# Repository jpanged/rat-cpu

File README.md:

# RAT CPU
*For CPE 233 Winter 2018*

**Russell Caletena, Josiah Pang, & Nathan Wang**

This repository contains all the parts that make up the RAT CPU as well as the software programs written in Assembly.

## [Learn more at our project website!](https://jpanged.github.io/rat-cpu/)

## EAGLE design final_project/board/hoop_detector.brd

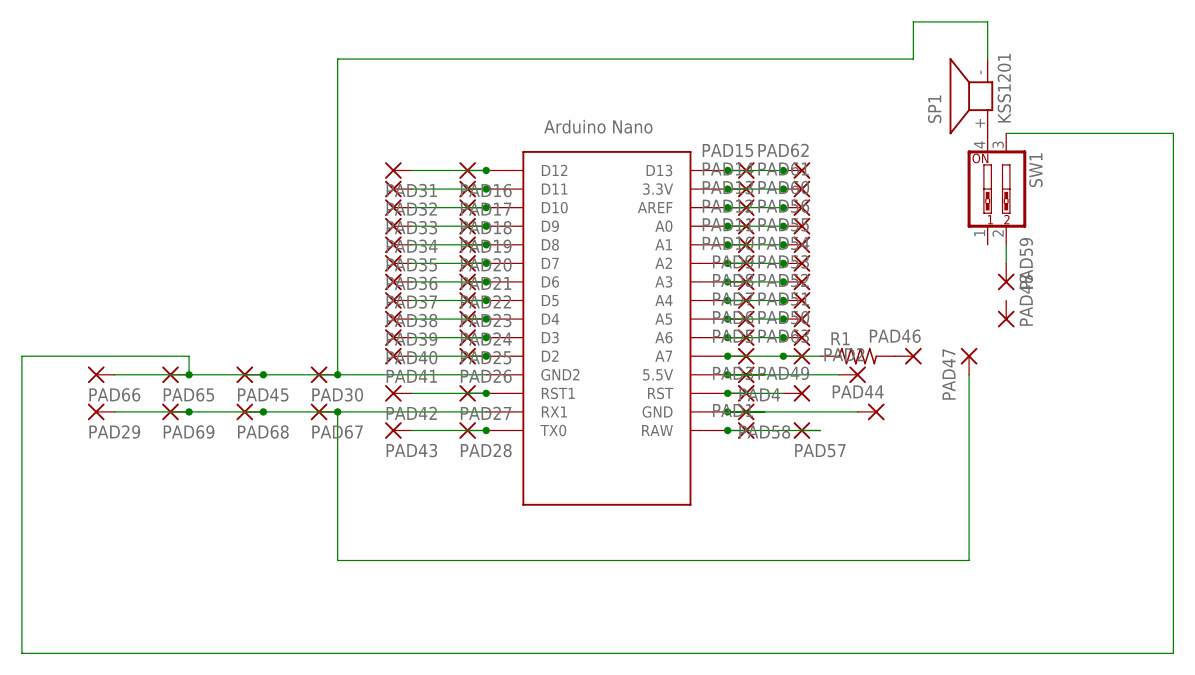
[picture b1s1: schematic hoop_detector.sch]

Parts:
PAD1, PAD2, PAD3, PAD4, PAD5, PAD6, PAD7, PAD8, PAD9, PAD10, PAD11, PAD12, PAD13, PAD14, PAD15, PAD16, PAD17, PAD18, PAD19, PAD20, PAD21, PAD22, PAD23, PAD24, PAD25, PAD26, PAD27, PAD28, PAD29, PAD30, PAD31, PAD32, PAD33, PAD34, PAD35, PAD36, PAD37, PAD38, PAD39, PAD40, PAD41, PAD42, PAD43, PAD44, PAD45, PAD46, PAD47, PAD48, PAD49, PAD50, PAD51, PAD52, PAD53, PAD54, PAD55, PAD56, PAD57, PAD58, PAD59, PAD60, PAD61, PAD62, PAD63, PAD65, PAD66, PAD67, PAD68, PAD69: 1,6/0,9
R1: R-US_0204/7; 0204/7
SP1: KSS1201
SW1: SW_DIP-2; EDG-02
U$1: NANO

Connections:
unnamed: PAD18.1, PAD33.1, U$1.D10
unnamed: PAD19.1, PAD34.1, U$1.D9
unnamed: PAD20.1, PAD35.1, U$1.D8
unnamed: PAD21.1, PAD36.1, U$1.D7
unnamed: PAD22.1, PAD37.1, U$1.D6
unnamed: PAD23.1, PAD38.1, U$1.D5
unnamed: PAD24.1, PAD39.1, U$1.D4
unnamed: PAD25.1, PAD40.1, U$1.D3
unnamed: PAD26.1, PAD41.1, U$1.D2
unnamed: PAD27.1, PAD42.1, U$1.RST1
unnamed: PAD28.1, PAD43.1, U$1.TX0
unnamed: PAD29.1, PAD47.1, PAD67.1, PAD68.1, PAD69.1, U$1.RX1
unnamed: PAD30.1, PAD45.1, PAD65.1, PAD66.1, SW1.3, U$1.GND1 (GND2)
unnamed: PAD16.1, PAD31.1, U$1.D12
unnamed: PAD17.1, PAD32.1, U$1.D11
unnamed: PAD59.1, SW1.2
unnamed: SP1.+ (1), SW1.4
unnamed: PAD5.1, PAD63.1, R1.1, U$1.A7
unnamed: PAD2.1, PAD4.1, U$1.5V (5.5V)
unnamed: PAD3.1, PAD49.1, U$1.RST
unnamed: PAD44.1, PAD58.1, U$1.GND
unnamed: PAD1.1, PAD57.1, U$1.RAW
unnamed: PAD46.1, R1.2
unnamed: PAD14.1, PAD61.1, U$1.3.3V
unnamed: PAD13.1, PAD60.1, U$1.AREF
unnamed: PAD12.1, PAD56.1, U$1.A0
unnamed: PAD10.1, PAD54.1, U$1.A2
unnamed: PAD9.1, PAD53.1, U$1.A3
unnamed: PAD8.1, PAD52.1, U$1.A4
unnamed: PAD7.1, PAD51.1, U$1.A5
unnamed: PAD6.1, PAD50.1, U$1.A6
unnamed: PAD11.1, PAD55.1, U$1.A1
unnamed: PAD15.1, PAD62.1, U$1.D13

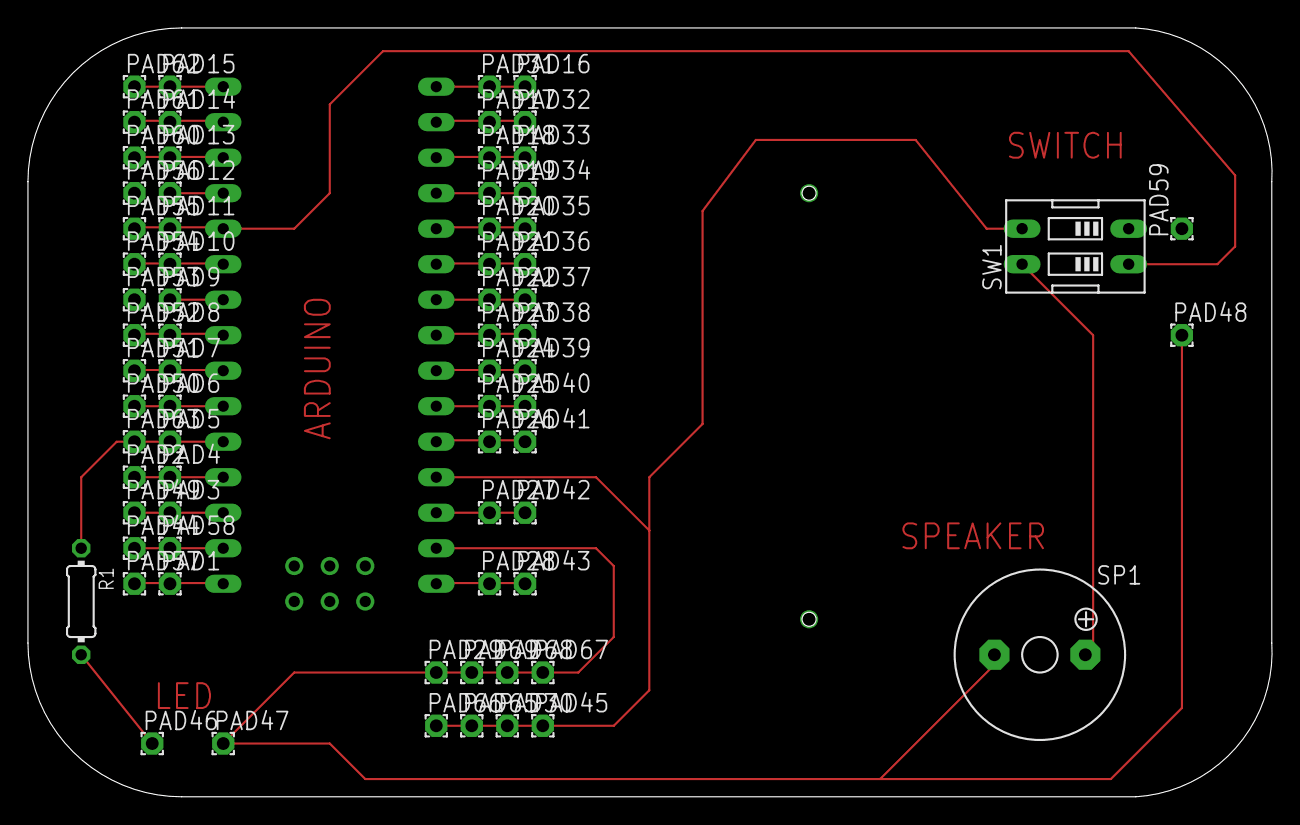
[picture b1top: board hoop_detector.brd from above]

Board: 2 copper layers, 89.0 x 55.0 mm, 72 parts (0 on the bottom side), 33 nets.

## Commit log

2018-01-10 Add sw1
2018-01-10 Finalize flowchart
2018-01-10 Working on sw1
2018-01-11 made commands lowercase
2018-01-11 FF HOOORAAYYYYgit add *git add * both parts are pinished!
2018-01-11 renamed this file, so this is no longer needed.
2018-01-12 updated flowchart
2018-01-12 pdf version of flowchart for sw1
2018-01-13 Fix some stuff
2018-01-16 Fix Github push problem from last week, repository up to date
2018-01-16 Remove sw1 prefix files
2018-01-17 Create sw2 directory
2018-01-17 Start framework for sw2
2018-01-17 Flowcharts
2018-01-18 finished sw2_1
2018-01-18 sw2 header
2018-01-18 Finish sw2 part 2
2018-01-19 Finish sw2 code
2018-01-19 removed one line for redundancy purposes
2018-01-19 start hw1
2018-01-19 fix sw2 flowchart
2018-01-20 made changes to headers of sw2 both parts
2018-01-21 HW1 SHOULD WORK
2018-01-23 Working
2018-01-23 HW1 Lab Report stuff
2018-01-24 Create structural model for rat2
2018-01-24 Add 2016.2 version of rat2
2018-01-24 Add 2016 version of rat2
2018-01-24 Started RAT 2 in Vivado
2018-01-24 RAT 2 code should work?
2018-01-24 Comments
2018-01-24 More comments
2018-01-25 Add testbench file
2018-01-25 test bench for rat 2
2018-01-25 Finish rat 2
2018-01-26 sw3 part 1 code and flowchart
2018-01-26 started flowchart and assembly for sw3_2
2018-01-26 Update sw3_2
2018-01-27 changes to parts 1 and 2 of sw3
2018-01-27 Working on sw3 flowchart
2018-01-27 Working on sw3
2018-01-27 modified function calling to part 1
2018-01-27 finalized part 1 with zero case
2018-01-27 finish sw3 flowchart
2018-01-27 sw3 images
2018-01-27 fixed part 2 register values
2018-01-29 started rat3
2018-01-29 further work on rat3 for parts 1 and 2
2018-01-29 started rat3 pt1 test bench
2018-01-29 changes to rat3 pt1 tb
2018-01-29 fix rat3 testbench
2018-01-29 started rat3 pt2 test bench
2018-01-29 testbench for rat3 part 2
2018-01-29 a couple sim things
2018-01-29 Add more test cases
2018-01-30 working on sim for rat3 report
2018-01-30 finalized tb rat3 pt2
2018-01-30 fix rat3
2018-01-31 Working on sw4
2018-01-31 working on sw4 flowchart
2018-01-31 modified sw4_1 by adding a reset to divide counter
2018-01-31 Fix sw4 part 2
2018-01-31 Fix sw4 flowchart
2018-01-31 Finish sw4
2018-01-31 Start vhdl for rat4
2018-01-31 Add pseudo code to other ALU cases
2018-02-02 added rat4 black box file
2018-02-02 Working on rat4
2018-02-02 clean up rat4, reduce redundancy
2018-02-02 finished test bench and vhd for rat4
2018-02-05 Add block diagram
2018-02-05 Create VHDL structure for spkr_drvr
2018-02-05 Add png file
2018-02-05 Add constraints file
2018-02-06 working on hw2
2018-02-06 hw2 working
2018-02-06 Add frequencies
2018-02-06 finish hw2
2018-02-06 added rat use case for hw2 to github
2018-02-07 Create initial files for rat5
2018-02-08 working on sw5
2018-02-08 sw5 part 1 flowchart
2018-02-08 code for sw5 should work
2018-02-08 updated flowchart for sw5p1 and made pdf
2018-02-09 made diagram for rat5 in visio
2018-02-09 Complete excel sheet and begin control unit fsm logic
2018-02-09 Control unit looks okay
2018-02-10 Prepare port map for rat_mcu
2018-02-10 sw5 flowcharts
2018-02-10 Port map mcu except for flags
2018-02-10 rat5 black box
2018-02-10 Debuggin errors and trying to fix mux issues
2018-02-10 rat5 complete
2018-02-11 rat5 black box finish
2018-02-11 Add simulation files from rat 5
2018-02-15 started vivado for hw3 and sw6
2018-02-15 sw6 pt 1
2018-02-15 finished sw6 pt2 with reset
2018-02-15 Start hw3
2018-02-15 sw6 code and flowchart
2018-02-15 fix rat2 naming thing
2018-02-15 fix sw6
2018-02-17 working on hw3
2018-02-17 Remove constraints file
2018-02-17 Implemenation of each row is complete, recognizing a button out of state is a work in progress
2018-02-17 More debugging on keypad numbers and output to leds
2018-02-18 Push for Nathan
2018-02-18 Nathan and Russell attempt hw3
2018-02-18 Testing
2018-02-18 More attempts at fsm
2018-02-19 More changes made
2018-02-20 add my broken hw3
2018-02-20 Add table for rat6
2018-02-20 Update rat6 table, create RAT_WRAPPER, and link inputs and outputs to constraints file
2018-02-20 Include latch files for fsm
2018-02-21 new hw3 file with tb
2018-02-21 Add working hw3
2018-02-21 rat6 stuff
2018-02-21 final comments for hw3
2018-02-21 hw3 use case and fsm chart
2018-02-21 working on rat6
2018-02-22 added test cases for rat 6 made prog rom chances to xpr
2018-02-22 ran all test cases for rat6 and black box diagram
2018-02-22 rat6 comments
2018-02-23 sw7 part 1
2018-02-23 add sw7
2018-02-23 sw7 part 2
2018-02-23 Add flowchart for part 1
2018-02-24 fix something
2018-02-24 fix sw7 part 2
2018-02-24 Update flowcharts
2018-02-24 initiated registers for sw7 pt2
2018-02-24 Finalize flowcharts
2018-02-24 Add png flowcharts
2018-02-26 start rat7
2018-02-27 work on mcu for rat 7, added sp and scr
2018-02-27 finalized rat 7 table of functions
2018-02-27 rat 7 working
2018-02-27 started sw8 files
2018-03-01 working on adding sseg part to rat7
2018-03-01 RAT 7 WORKS
2018-03-02 sw8 part 1
2018-03-03 work on sw8 part 2
2018-03-03 completed sw8 pt2
2018-03-03 sw8 part 1 flowchart
2018-03-03 minor text fixes
2018-03-03 made sw8 pt2 flowchart
2018-03-04 completed rat8
2018-03-05 start hw4
2018-03-05 Add black box diagram for int_controller
2018-03-05 hw4 stuff
2018-03-05 Update black box
2018-03-05 create rat mcu vivado program
2018-03-06 Port map interrupt controller and change constraints file for switches
2018-03-06 wrote asm program for hw4
2018-03-06 moved asm back to original location
2018-03-06 fix rat_mcu folder
2018-03-06 asdf
2018-03-06 recreated new asm file
2018-03-06 reorganizing hw4 asm folder
2018-03-06 finished hardware 4
2018-03-08 start final project stuff
2018-03-08 more final project stuff
2018-03-09 arduino stuff
2018-03-10 hoop counter works!!
2018-03-13 working on final project
2018-03-13 made timer
2018-03-13 fix repo
2018-03-13 game clock made
2018-03-13 board
2018-03-14 finish board pcb
2018-03-15 got score counter to work
2018-03-16 diagram
2018-03-16 made rest of diagrams, commented and renamed files in vhd
2018-03-16 Set theme jekyll-theme-cayman
2018-03-16 test for pages
2018-03-16 move config
2018-03-16 Set theme jekyll-theme-slate
2018-03-16 remove docs
2018-03-16 docs folder
2018-03-16 test adding page
2018-03-16 index
2018-03-16 remove index
2018-03-17 sw1 pages
2018-03-17 test
2018-03-17 'button'
2018-03-17 info
2018-03-17 sw3 and sw4
2018-03-17 titles
2018-03-17 final project page
2018-03-17 finish adding sw pages
2018-03-17 hardware project pages
2018-03-17 Add rat pages
2018-03-18 updating project site
2018-03-18 table
2018-03-18 formatting
2018-03-18 readme
2018-03-18 footer
2018-03-18 add vids
2018-03-18 trying
2018-03-18 favicon
2018-03-18 button for source code
2018-03-18 color
2018-03-18 minor changes
2018-03-18 update index
2018-03-18 fix demo links
2018-03-19 added context sections
